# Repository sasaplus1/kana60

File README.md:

# kana60

JP layout 60% mechanical keyboard

Keycaps: [FILCO FKCS108NMP](https://www.amazon.co.jp/dp/B07SR3NHXY/) and another 1 keycap (At bottom of N key).

QMK Firmware: [sasaplus1/qmk_firmware](https://github.com/qmk/qmk_firmware/compare/master...sasaplus1:kana60-test)

## How to verify checksums

```console
$ ls -1
kana60-acrylic-plates.zip
kana60-sha256sum.txt
kana60-top-plate.zip
kana60.zip
$ shasum --check kana60-sha256sum.txt
kana60-acrylic-plates.zip: OK
kana60.zip: OK
kana60-top-plate.zip: OK
```

## How to release

remove dist files:

```console
$ make clean
```

generate some files:

- open `kana60.kicad_pcb` and generate gerber files and drill files, via: `plot...`
- open `kana60-top-plate.kicad_pcb` and generate gerber files and drill files, via: `plot...`
- open `kana60-acrylic-plates.kicad_pcb` and generate PDF files, via: `plot...`

generate zip files and checksum file:

```console
$ make build create_checksum
```

verify zip files:

```console
$ make info
zipinfo dist/kana60-acrylic-plates/kana60-acrylic-plates.zip
Archive:  dist/kana60-acrylic-plates/kana60-acrylic-plates.zip
Zip file size: 22152 bytes, number of entries: 2
-rw-r--r--  3.0 unx     3150 bx defN 19-Oct-27 17:44 kana60-acrylic-plates-main.pdf
-rw-r--r--  3.0 unx    20236 bx defN 19-Oct-27 17:44 kana60-acrylic-plates-dimensions.pdf
2 files, 23386 bytes uncompressed, 21742 bytes compressed:  7.0%
zipinfo dist/kana60/kana60.zip
Archive:  dist/kana60/kana60.zip
Zip file size: 455650 bytes, number of entries: 9
-rw-r--r--  3.0 unx   807098 tx defN 19-Oct-27 17:44 kana60.GBL
-rw-r--r--  3.0 unx   293239 tx defN 19-Oct-27 17:44 kana60.GBS
-rw-r--r--  3.0 unx    49400 tx defN 19-Oct-27 17:44 kana60.GBO
-rw-r--r--  3.0 unx      980 tx defN 19-Oct-27 17:44 kana60.GML
-rw-r--r--  3.0 unx   522285 tx defN 19-Oct-27 17:44 kana60.GTL
-rw-r--r--  3.0 unx   293239 tx defN 19-Oct-27 17:44 kana60.GTS
-rw-r--r--  3.0 unx    88481 tx defN 19-Oct-27 17:44 kana60.GTO
-rw-r--r--  3.0 unx     4210 tx defN 19-Oct-27 17:44 kana60-NPTH.TXT
-rw-r--r--  3.0 unx    11536 tx defN 19-Oct-27 17:44 kana60.TXT
9 files, 2070468 bytes uncompressed, 454286 bytes compressed:  78.1%
zipinfo dist/kana60-top-plate/kana60-top-plate.zip
Archive:  dist/kana60-top-plate/kana60-top-plate.zip
Zip file size: 93042 bytes, number of entries: 9
-rw-r--r--  3.0 unx   201454 tx defN 19-Oct-27 17:44 kana60-top-plate.GBL
-rw-r--r--  3.0 unx     5359 tx defN 19-Oct-27 17:44 kana60-top-plate.GBS
-rw-r--r--  3.0 unx    11104 tx defN 19-Oct-27 17:44 kana60-top-plate.GBO
-rw-r--r--  3.0 unx    19886 tx defN 19-Oct-27 17:44 kana60-top-plate.GML
-rw-r--r--  3.0 unx   201454 tx defN 19-Oct-27 17:44 kana60-top-plate.GTL
-rw-r--r--  3.0 unx     5359 tx defN 19-Oct-27 17:44 kana60-top-plate.GTS
-rw-r--r--  3.0 unx      506 tx defN 19-Oct-27 17:44 kana60-top-plate.GTO
-rw-r--r--  3.0 unx      296 tx defN 19-Oct-27 17:44 kana60-top-plate-NPTH.TXT
-rw-r--r--  3.0 unx      388 tx defN 19-Oct-27 17:44 kana60-top-plate.TXT
9 files, 445806 bytes uncompressed, 91498 bytes compressed:  79.5%
```

push tag to GitHub and create Release:

```console
$ git tag 1.0
$ git push origin 1.0
```

upload files:

- kana60-acrylic-plates.zip
- kana60-sha256sum.txt
- kana60-top-plate.zip
- kana60.zip

## License

The MIT license.

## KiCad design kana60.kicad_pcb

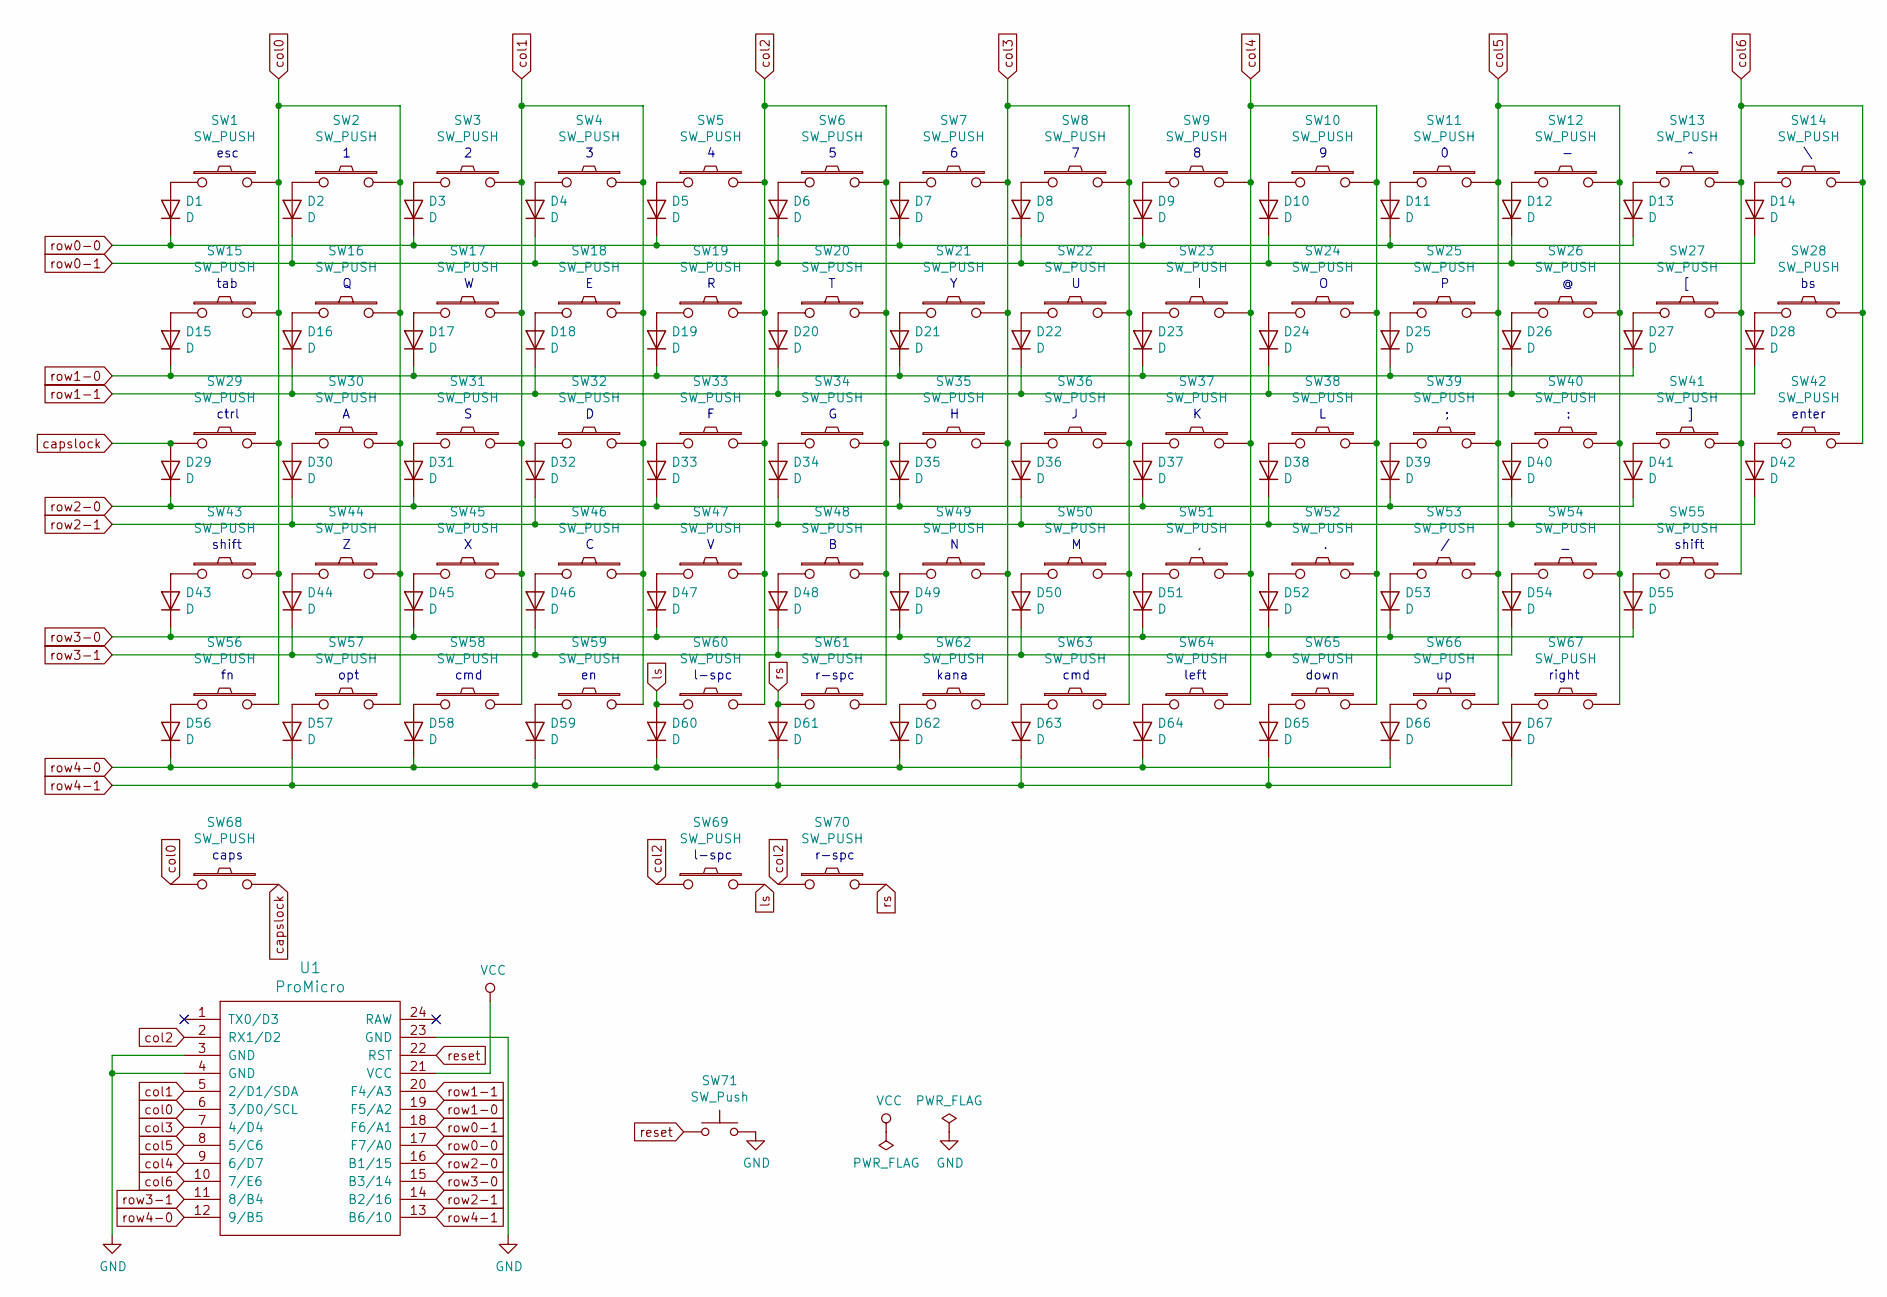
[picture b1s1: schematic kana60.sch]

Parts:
D1, D2, D3, D4, D5, D6, D7, D8, D9, D10, D11, D12, D13, D14, D15, D16, D17, D18, D19, D20, D21, D22, D23, D24, D25, D26, D27, D28, D29, D30, D31, D32, D33, D34, D35, D36, D37, D38, D39, D40, D41, D42, D43, D44, D45, D46, D47, D48, D49, D50, D51, D52, D53, D54, D55, D56, D57, D58, D59, D60, D61, D62, D63, D64, D65, D66, D67: D; diode
SW1, SW2, SW3, SW4, SW5, SW6, SW7, SW8, SW9, SW10, SW11, SW12, SW13, SW14, SW16, SW17, SW18, SW19, SW20, SW21, SW22, SW23, SW24, SW25, SW26, SW27, SW28, SW30, SW31, SW32, SW33, SW34, SW35, SW36, SW37, SW38, SW39, SW40, SW41, SW44, SW45, SW46, SW47, SW48, SW49, SW50, SW51, SW52, SW53, SW54, SW61, SW64, SW65, SW66, SW67, SW68, SW69: SW_PUSH; Hybrid_PCB_100H
SW15: SW_PUSH; Hybrid_PCB_150H
SW29, SW55: SW_PUSH; Hybrid_PCB_175H
SW42, SW43, SW60, SW70: SW_PUSH; Hybrid_PCB_200H
SW56, SW57, SW58, SW59, SW62, SW63: SW_PUSH; Hybrid_PCB_125H
SW71: SW_Push; SW_Tactile_SPST_Angled_MJTP1117
U1: ProMicro; ArduinoProMicro

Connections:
GND: SW71.2, U1.3 (GND), U1.4 (GND), U1.23 (GND)
unnamed: D1.2 (A), SW1.1
unnamed: D2.2 (A), SW2.1
unnamed: D3.2 (A), SW3.1
unnamed: D4.2 (A), SW4.1
unnamed: D5.2 (A), SW5.1
unnamed: D6.2 (A), SW6.1
unnamed: D7.2 (A), SW7.1
unnamed: D8.2 (A), SW8.1
unnamed: D9.2 (A), SW9.1
unnamed: D10.2 (A), SW10.1
unnamed: D11.2 (A), SW11.1
unnamed: D12.2 (A), SW12.1
unnamed: D13.2 (A), SW13.1
unnamed: D14.2 (A), SW14.1
unnamed: D15.2 (A), SW15.1
unnamed: D16.2 (A), SW16.1
unnamed: D17.2 (A), SW17.1
unnamed: D18.2 (A), SW18.1
unnamed: D19.2 (A), SW19.1
unnamed: D20.2 (A), SW20.1
unnamed: D21.2 (A), SW21.1
unnamed: D22.2 (A), SW22.1
unnamed: D23.2 (A), SW23.1
unnamed: D24.2 (A), SW24.1
unnamed: D25.2 (A), SW25.1
unnamed: D26.2 (A), SW26.1
unnamed: D27.2 (A), SW27.1
unnamed: D28.2 (A), SW28.1
unnamed: D30.2 (A), SW30.1
unnamed: D31.2 (A), SW31.1
unnamed: D32.2 (A), SW32.1
unnamed: D33.2 (A), SW33.1
unnamed: D34.2 (A), SW34.1
unnamed: D35.2 (A), SW35.1
unnamed: D36.2 (A), SW36.1
unnamed: D37.2 (A), SW37.1
unnamed: D38.2 (A), SW38.1
unnamed: D39.2 (A), SW39.1
unnamed: D40.2 (A), SW40.1
unnamed: D41.2 (A), SW41.1
unnamed: D42.2 (A), SW42.1
unnamed: D43.2 (A), SW43.1
unnamed: D44.2 (A), SW44.1
unnamed: D45.2 (A), SW45.1
unnamed: D46.2 (A), SW46.1
unnamed: D47.2 (A), SW47.1
unnamed: D48.2 (A), SW48.1
unnamed: D49.2 (A), SW49.1
unnamed: D50.2 (A), SW50.1
unnamed: D51.2 (A), SW51.1
unnamed: D52.2 (A), SW52.1
unnamed: D53.2 (A), SW53.1
unnamed: D54.2 (A), SW54.1
unnamed: D55.2 (A), SW55.1
unnamed: D56.2 (A), SW56.1
unnamed: D57.2 (A), SW57.1
unnamed: D58.2 (A), SW58.1
unnamed: D59.2 (A), SW59.1
unnamed: D62.2 (A), SW62.1
unnamed: D63.2 (A), SW63.1
unnamed: D64.2 (A), SW64.1
unnamed: D65.2 (A), SW65.1
unnamed: D66.2 (A), SW66.1
unnamed: D67.2 (A), SW67.1
VCC: U1.21 (VCC)
capslock: D29.2 (A), SW29.1, SW68.2
col0: SW1.2, SW2.2, SW15.2, SW16.2, SW29.2, SW30.2, SW43.2, SW44.2, SW56.2, SW57.2, SW68.1, U1.6 (3/D0/SCL)
col1: SW3.2, SW4.2, SW17.2, SW18.2, SW31.2, SW32.2, SW45.2, SW46.2, SW58.2, SW59.2, U1.5 (2/D1/SDA)
col2: SW5.2, SW6.2, SW19.2, SW20.2, SW33.2, SW34.2, SW47.2, SW48.2, SW60.2, SW61.2, SW69.1, SW70.1, U1.2 (RX1/D2)
col3: SW7.2, SW8.2, SW21.2, SW22.2, SW35.2, SW36.2, SW49.2, SW50.2, SW62.2, SW63.2, U1.7 (4/D4)
col4: SW9.2, SW10.2, SW23.2, SW24.2, SW37.2, SW38.2, SW51.2, SW52.2, SW64.2, SW65.2, U1.9 (6/D7)
col5: SW11.2, SW12.2, SW25.2, SW26.2, SW39.2, SW40.2, SW53.2, SW54.2, SW66.2, SW67.2, U1.8 (5/C6)
col6: SW13.2, SW14.2, SW27.2, SW28.2, SW41.2, SW42.2, SW55.2, U1.10 (7/E6)
ls: D60.2 (A), SW60.1, SW69.2
reset: SW71.1, U1.22 (RST)
row0-0: D1.1 (K), D3.1 (K), D5.1 (K), D7.1 (K), D9.1 (K), D11.1 (K), D13.1 (K), U1.17 (F7/A0)
row0-1: D2.1 (K), D4.1 (K), D6.1 (K), D8.1 (K), D10.1 (K), D12.1 (K), D14.1 (K), U1.18 (F6/A1)
row1-0: D15.1 (K), D17.1 (K), D19.1 (K), D21.1 (K), D23.1 (K), D25.1 (K), D27.1 (K), U1.19 (F5/A2)
row1-1: D16.1 (K), D18.1 (K), D20.1 (K), D22.1 (K), D24.1 (K), D26.1 (K), D28.1 (K), U1.20 (F4/A3)
row2-0: D29.1 (K), D31.1 (K), D33.1 (K), D35.1 (K), D37.1 (K), D39.1 (K), D41.1 (K), U1.16 (B1/15)
row2-1: D30.1 (K), D32.1 (K), D34.1 (K), D36.1 (K), D38.1 (K), D40.1 (K), D42.1 (K), U1.14 (B2/16)
row3-0: D43.1 (K), D45.1 (K), D47.1 (K), D49.1 (K), D51.1 (K), D53.1 (K), D55.1 (K), U1.15 (B3/14)
row3-1: D44.1 (K), D46.1 (K), D48.1 (K), D50.1 (K), D52.1 (K), D54.1 (K), U1.11 (8/B4)
row4-0: D56.1 (K), D58.1 (K), D60.1 (K), D62.1 (K), D64.1 (K), D66.1 (K), U1.12 (9/B5)
row4-1: D57.1 (K), D59.1 (K), D61.1 (K), D63.1 (K), D65.1 (K), D67.1 (K), U1.13 (B6/10)
rs: D61.2 (A), SW61.1, SW70.2

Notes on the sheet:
esc
tab
ctrl
shift
opt
cmd
l-spc
kana
left
down
right
enter
r-spc
caps

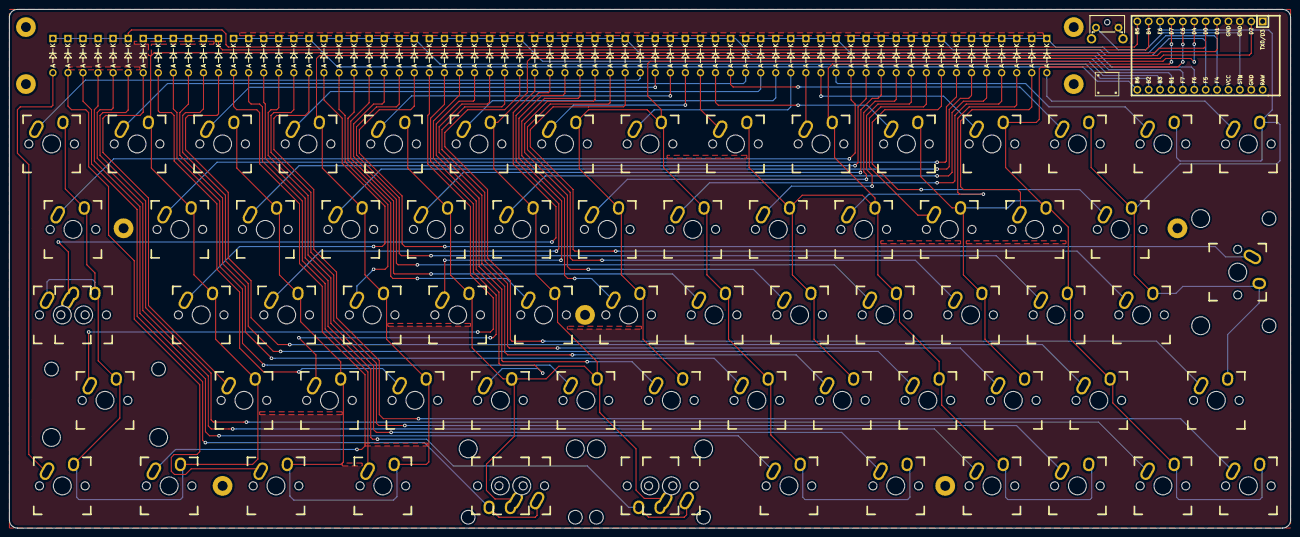
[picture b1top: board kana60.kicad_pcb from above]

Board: 2 copper layers, 285.5 x 115.6 mm, 148 parts (0 on the bottom side), 86 nets.

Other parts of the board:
REF1, REF2, REF3, REF4, REF5, REF6, REF7, REF8, REF9: MountingHole_2.2mm_M2_Pad

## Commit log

2019-06-16 add README.md
2019-06-16 add .gitignore
2019-06-16 create KiCad project
2019-06-18 add libs
2019-06-18 add KiCad files
2019-06-18 add ProMicro and reset switch
2019-06-30 add key switches
2019-06-30 annotation and rule check
2019-06-30 fix footprint
2019-07-01 add PCB footprint
2019-07-01 add pdf
2019-07-01 add Keebio-Parts.pretty
2019-07-01 change to use project local library
2019-07-02 update pdf
2019-07-02 update label
2019-07-02 reannotate
2019-07-04 remove extra diode
2019-07-05 change footprint
2019-07-07 add footprint
2019-07-07 update pcb
2019-07-07 update schematic
2019-07-24 remove footprint
2019-07-24 update footprint
2019-07-30 add trace width
2019-07-30 fix schematic
2019-07-31 add net classes
2019-08-01 change to use through hole diode
2019-09-25 trial and error
2019-09-25 reposition
2019-09-25 hide silks
2019-09-25 reassign grid origin
2019-09-25 add logo
2019-09-25 add title
2019-09-25 rotate reset switch
2019-09-25 add text
2019-09-25 connection complete
2019-09-25 update kbd libs
2019-09-25 update keebio libs
2019-09-28 add footprints
2019-09-28 rename diectory
2019-09-28 update remote URL of submodule
2019-09-28 update library paths
2019-09-28 remove resource
2019-09-28 move local footprints
2019-09-28 update library path
2019-09-28 update netlist
2019-09-28 update library
2019-09-28 update footprints
2019-09-28 move icon position
2019-09-28 add top plate
2019-09-28 remove extra footprints
2019-09-29 update top plate
2019-09-29 add acrylic plates
2019-09-29 add bottom acrylic plate
2019-09-30 update acrylic plates
2019-10-02 rewrite Edge.Cuts
2019-10-02 change to Cmts.User from Dwgs.User
2019-10-02 add dimention lines
2019-10-02 add GND plane
2019-10-03 trim anntena
2019-10-03 add dist directory
2019-10-03 update output directory
2019-10-04 add Makefile
2019-10-04 update dimention lines
2019-10-04 move lines into frame
2019-10-04 add acrylic targets
2019-10-04 add LICENSE
2019-10-04 add License section
2019-10-04 add description
2019-10-04 ignore subdirectories when packaging
2019-10-12 add plane to top plate
2019-10-12 change revision to 1.1 from 1.0
2019-10-12 add create_checksum target
2019-10-12 ignore checksum file
2019-10-24 fix stabilizer interfere
2019-10-24 update captions
2019-10-26 add label to top plate
2019-10-26 update submodule
2019-10-26 add icon to top plate
2019-10-26 update icon
2019-10-26 update GND plane
2019-10-26 change tactile button
2019-10-26 rotate space bar switches for fix stabilizer
2019-10-27 update GND plane and wiring
2019-10-27 add HISTORY.md
2020-06-16 add .gitattributes
2020-12-10 add CADLAB.io badge
2021-03-27 add kana60's photo and keycaps information
2021-03-27 add firmware's link
